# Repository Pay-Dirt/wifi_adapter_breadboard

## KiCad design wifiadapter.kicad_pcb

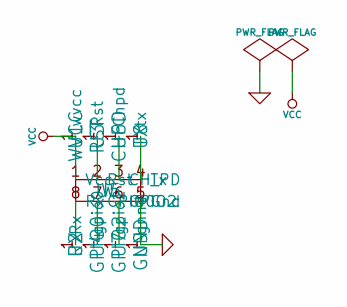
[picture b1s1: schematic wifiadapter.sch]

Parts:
U1: WVCC
U2: RX
U3: RST
U4: GPIO0
U5: W
U6: CHPD
U7: GPIO2
U8: TX
U9: GNND

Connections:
GND: U5.5 (Gnd), U9.1
unnamed: U2.1, U5.8 (Rx)
unnamed: U4.1, U5.7 (GPIO0)
unnamed: U5.6 (GPIO2), U7.1
unnamed: U5.4 (Tx), U8.1
unnamed: U5.3 (CH_PD), U6.1
unnamed: U3.1, U5.2 (Rst)
VCC: U1.1, U5.1 (Vcc)

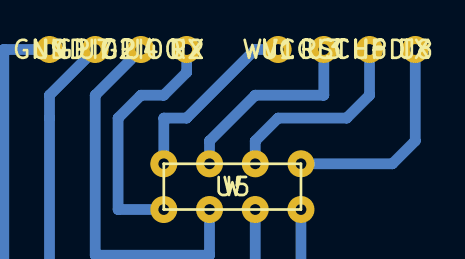
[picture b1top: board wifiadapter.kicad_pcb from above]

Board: 2 copper layers, 9 parts (0 on the bottom side), 8 nets.

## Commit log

2015-04-17 Initial phase complete
